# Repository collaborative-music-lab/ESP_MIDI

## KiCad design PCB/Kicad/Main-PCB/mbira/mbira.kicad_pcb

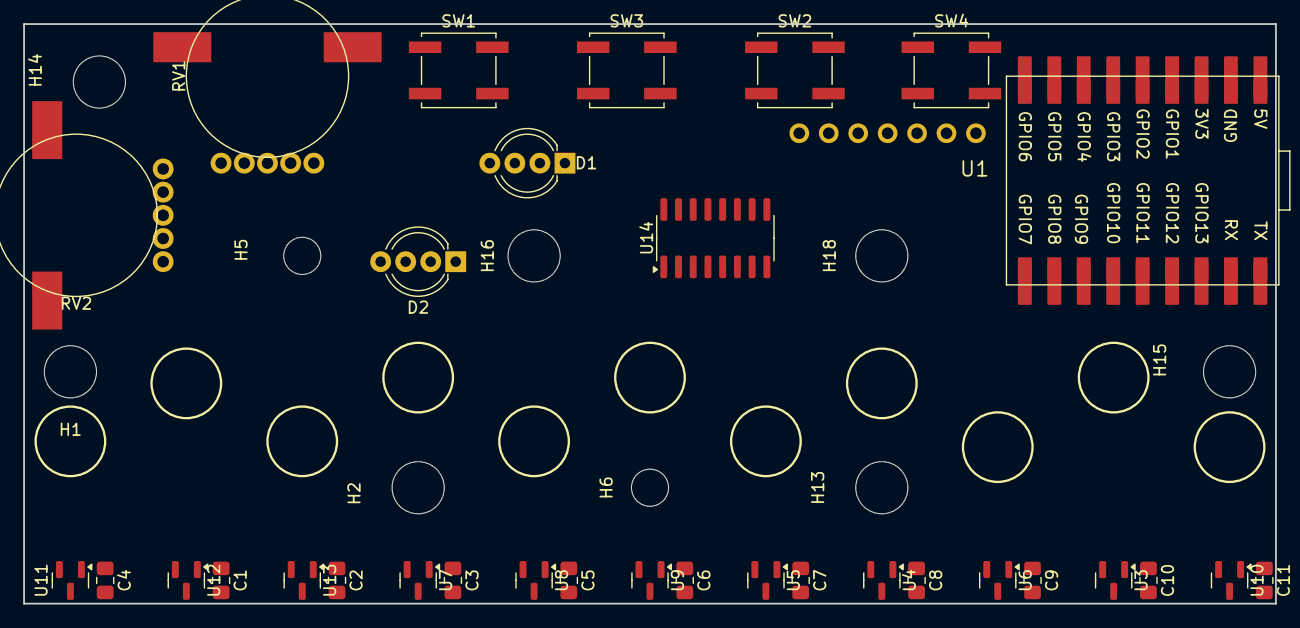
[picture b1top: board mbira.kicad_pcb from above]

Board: 2 copper layers, 108.0 x 50.0 mm, 42 parts (0 on the bottom side), 18 nets, no tracks yet.

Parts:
C1, C2, C3, C4, C5, C6, C7, C8, C9, C10, C11: 0.1uF; C_0805_2012Metric_Pad1.18x1.45mm_HandSolder
D1, D2: WS2812B; LED_D5.0mm-4_RGB_Wide_Pins
H1, H2, H13, H14, H15, H16, H18: MountingHole; MountingHole_4.5mm
H5, H6: MountingHole; MountingHole_3.2mm_M3_ISO14580
RV1, RV2: R_Potentiometer_Dual; potentiometer_wheel_10mm_SMD-shield
SW1, SW2, SW3, SW4: SW_DPST; SW_Push_1P1T_NO_CK_KSC6xxJ
U1: LSM6DS3_Breakout; LSM6DS3_Breakout_oneSide
U2: Wifiduino-ESP32S3-SMD
U3, U4, U5, U6, U7, U8, U9, U10, U11, U12, U13: SM351LT; SOT-23
U14: MCP3208; SOIC-16_3.9x9.9mm_P1.27mm

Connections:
+3.3V: C1.1, C2.1, C3.1, C4.1, C5.1, C6.1, C7.1, C8.1, C9.1, C10.1, C11.1, D1.3 (VDD), D2.3 (VDD), RV1.1 (1A), RV2.1 (1A), U1.1 (VIN), U2.3 (3V3), U3.1 (VCC), U4.1 (VCC), U5.1 (VCC), U6.1 (VCC), U7.1 (VCC), U8.1 (VCC), U9.1 (VCC), U10.1 (VCC), U11.1 (VCC), U12.1 (VCC), U13.1 (VCC)
/A0: U2.4 (GPIO1/ADC1_CH0), U3.2 (OUTPUT)
/A1: U2.5 (GPIO2/ADC1_CH1), U4.2 (OUTPUT)
/A2: U2.6 (GPIO3/ADC1_CH2), U5.2 (OUTPUT)
/A3: U2.7 (GPIO4/ADC1_CH3), U6.2 (OUTPUT)
/A4: U2.8 (GPIO5/ADC1_CH4), U7.2 (OUTPUT)
/A5: U2.9 (GPIO6/ADC1_CH5), U8.2 (OUTPUT)
/A6: U2.10 (GPIO7/ADC1_CH6), U9.2 (OUTPUT)
/A7: U2.11 (GPIO8/ADC1_CH7), U10.2 (OUTPUT)
/A8: U2.12 (GPIO9/ADC1_CH8), U11.2 (OUTPUT)
/A9: U2.13 (GPIO10/ADC1_CH9), U12.2 (OUTPUT)
/A10: U2.16 (GPIO13/ADC2_CH2), U13.2 (OUTPUT)
/A11: RV1.6 (Shield), RV2.6 (Shield), U2.15 (GPIO12/ADC2_CH1)
/D0: D1.4 (DIN), U2.14 (GPIO11/ADC2_CH0)
/SCL: U1.4 (SCL), U2.18 (GPIO43/U0TXD)
/SDA: U1.5 (SDA), U2.17 (GPIO44/U0RXD)
GND: C1.2, C2.2, C3.2, C4.2, C5.2, C6.2, C7.2, C8.2, C9.2, C10.2, C11.2, D1.2 (VSS), D2.2 (VSS), RV1.5 (Common), RV2.5 (Common), U1.3 (GND), U2.2 (GND), U3.3 (GND), U4.3 (GND), U5.3 (GND), U6.3 (GND), U7.3 (GND), U8.3 (GND), U9.3 (GND), U10.3 (GND), U11.3 (GND), U12.3 (GND), U13.3 (GND)
unnamed: D1.1 (DOUT), D2.4 (DIN)

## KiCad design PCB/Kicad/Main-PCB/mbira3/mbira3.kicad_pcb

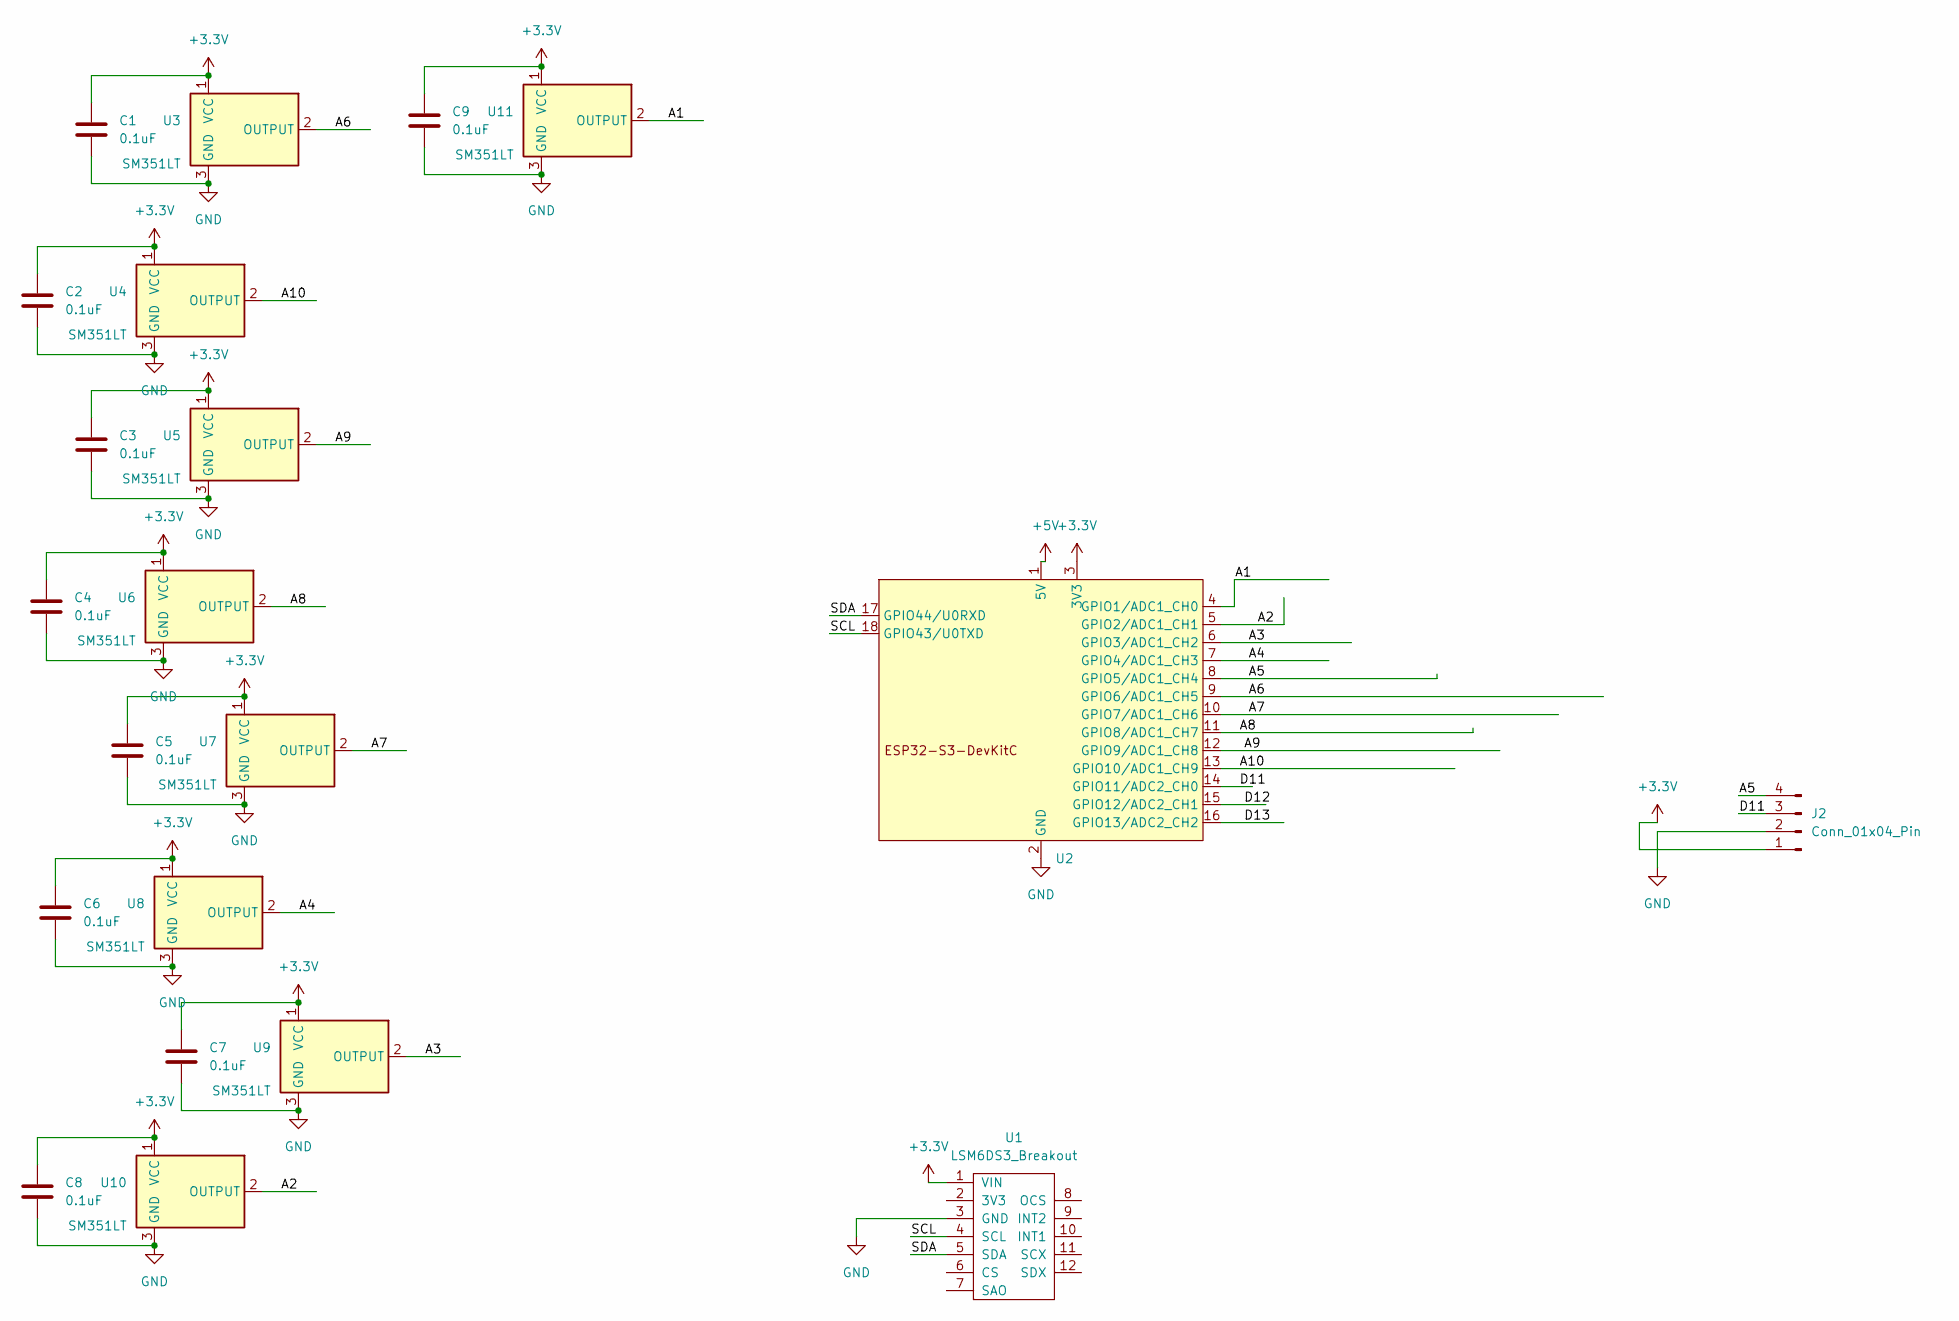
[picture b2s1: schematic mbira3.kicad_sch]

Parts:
C1, C2, C3, C4, C5, C6, C7, C8, C9: 0.1uF; C_0805_2012Metric_Pad1.18x1.45mm_HandSolder
J2: Conn_01x04_Pin; PinHeader_1x04_P1.27mm_Vertical
U1: LSM6DS3_Breakout; LSM6DS3_Breakout_oneSide
U2: Wifiduino-ESP32S3-SMD
U3, U4, U5, U6, U7, U8, U9, U10, U11: SM351LT; SOT-23

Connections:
+3.3V: C1.1, C2.1, C3.1, C4.1, C5.1, C6.1, C7.1, C8.1, C9.1, J2.1, U1.1 (VIN), U2.3 (3V3), U3.1 (VCC), U4.1 (VCC), U5.1 (VCC), U6.1 (VCC), U7.1 (VCC), U8.1 (VCC), U9.1 (VCC), U10.1 (VCC), U11.1 (VCC)
+5V: U2.1 (5V)
/A1: U2.4 (GPIO1/ADC1_CH0), U11.2 (OUTPUT)
/A2: U2.5 (GPIO2/ADC1_CH1), U10.2 (OUTPUT)
/A3: U2.6 (GPIO3/ADC1_CH2), U9.2 (OUTPUT)
/A4: U2.7 (GPIO4/ADC1_CH3), U8.2 (OUTPUT)
/A5: J2.4, U2.8 (GPIO5/ADC1_CH4)
/A6: U2.9 (GPIO6/ADC1_CH5), U3.2 (OUTPUT)
/A7: U2.10 (GPIO7/ADC1_CH6), U7.2 (OUTPUT)
/A8: U2.11 (GPIO8/ADC1_CH7), U6.2 (OUTPUT)
/A9: U2.12 (GPIO9/ADC1_CH8), U5.2 (OUTPUT)
/A10: U2.13 (GPIO10/ADC1_CH9), U4.2 (OUTPUT)
/D11: J2.3, U2.14 (GPIO11/ADC2_CH0)
/D12: U2.15 (GPIO12/ADC2_CH1)
/D13: U2.16 (GPIO13/ADC2_CH2)
/SCL: U1.4 (SCL), U2.18 (GPIO43/U0TXD)
/SDA: U1.5 (SDA), U2.17 (GPIO44/U0RXD)
GND: C1.2, C2.2, C3.2, C4.2, C5.2, C6.2, C7.2, C8.2, C9.2, J2.2, U1.3 (GND), U2.2 (GND), U3.3 (GND), U4.3 (GND), U5.3 (GND), U6.3 (GND), U7.3 (GND), U8.3 (GND), U9.3 (GND), U10.3 (GND), U11.3 (GND)

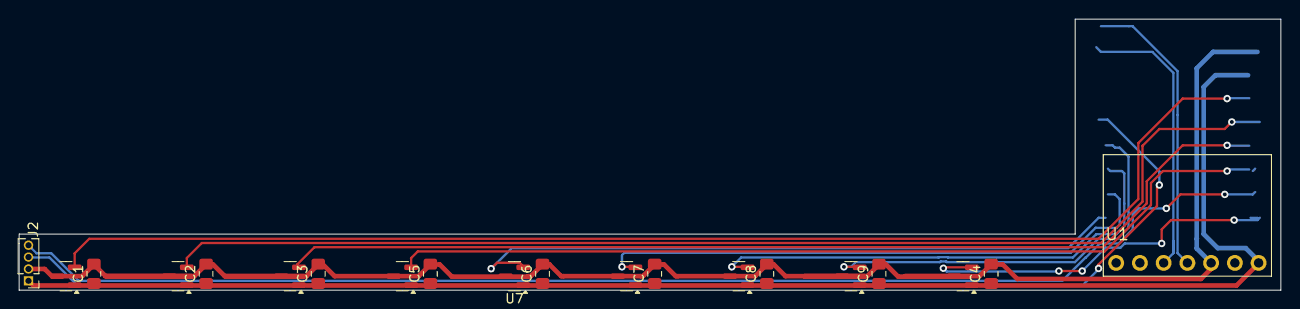
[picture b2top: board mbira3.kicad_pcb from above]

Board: 2 copper layers, 135.0 x 29.0 mm, 21 parts (1 on the bottom side), 15 nets.

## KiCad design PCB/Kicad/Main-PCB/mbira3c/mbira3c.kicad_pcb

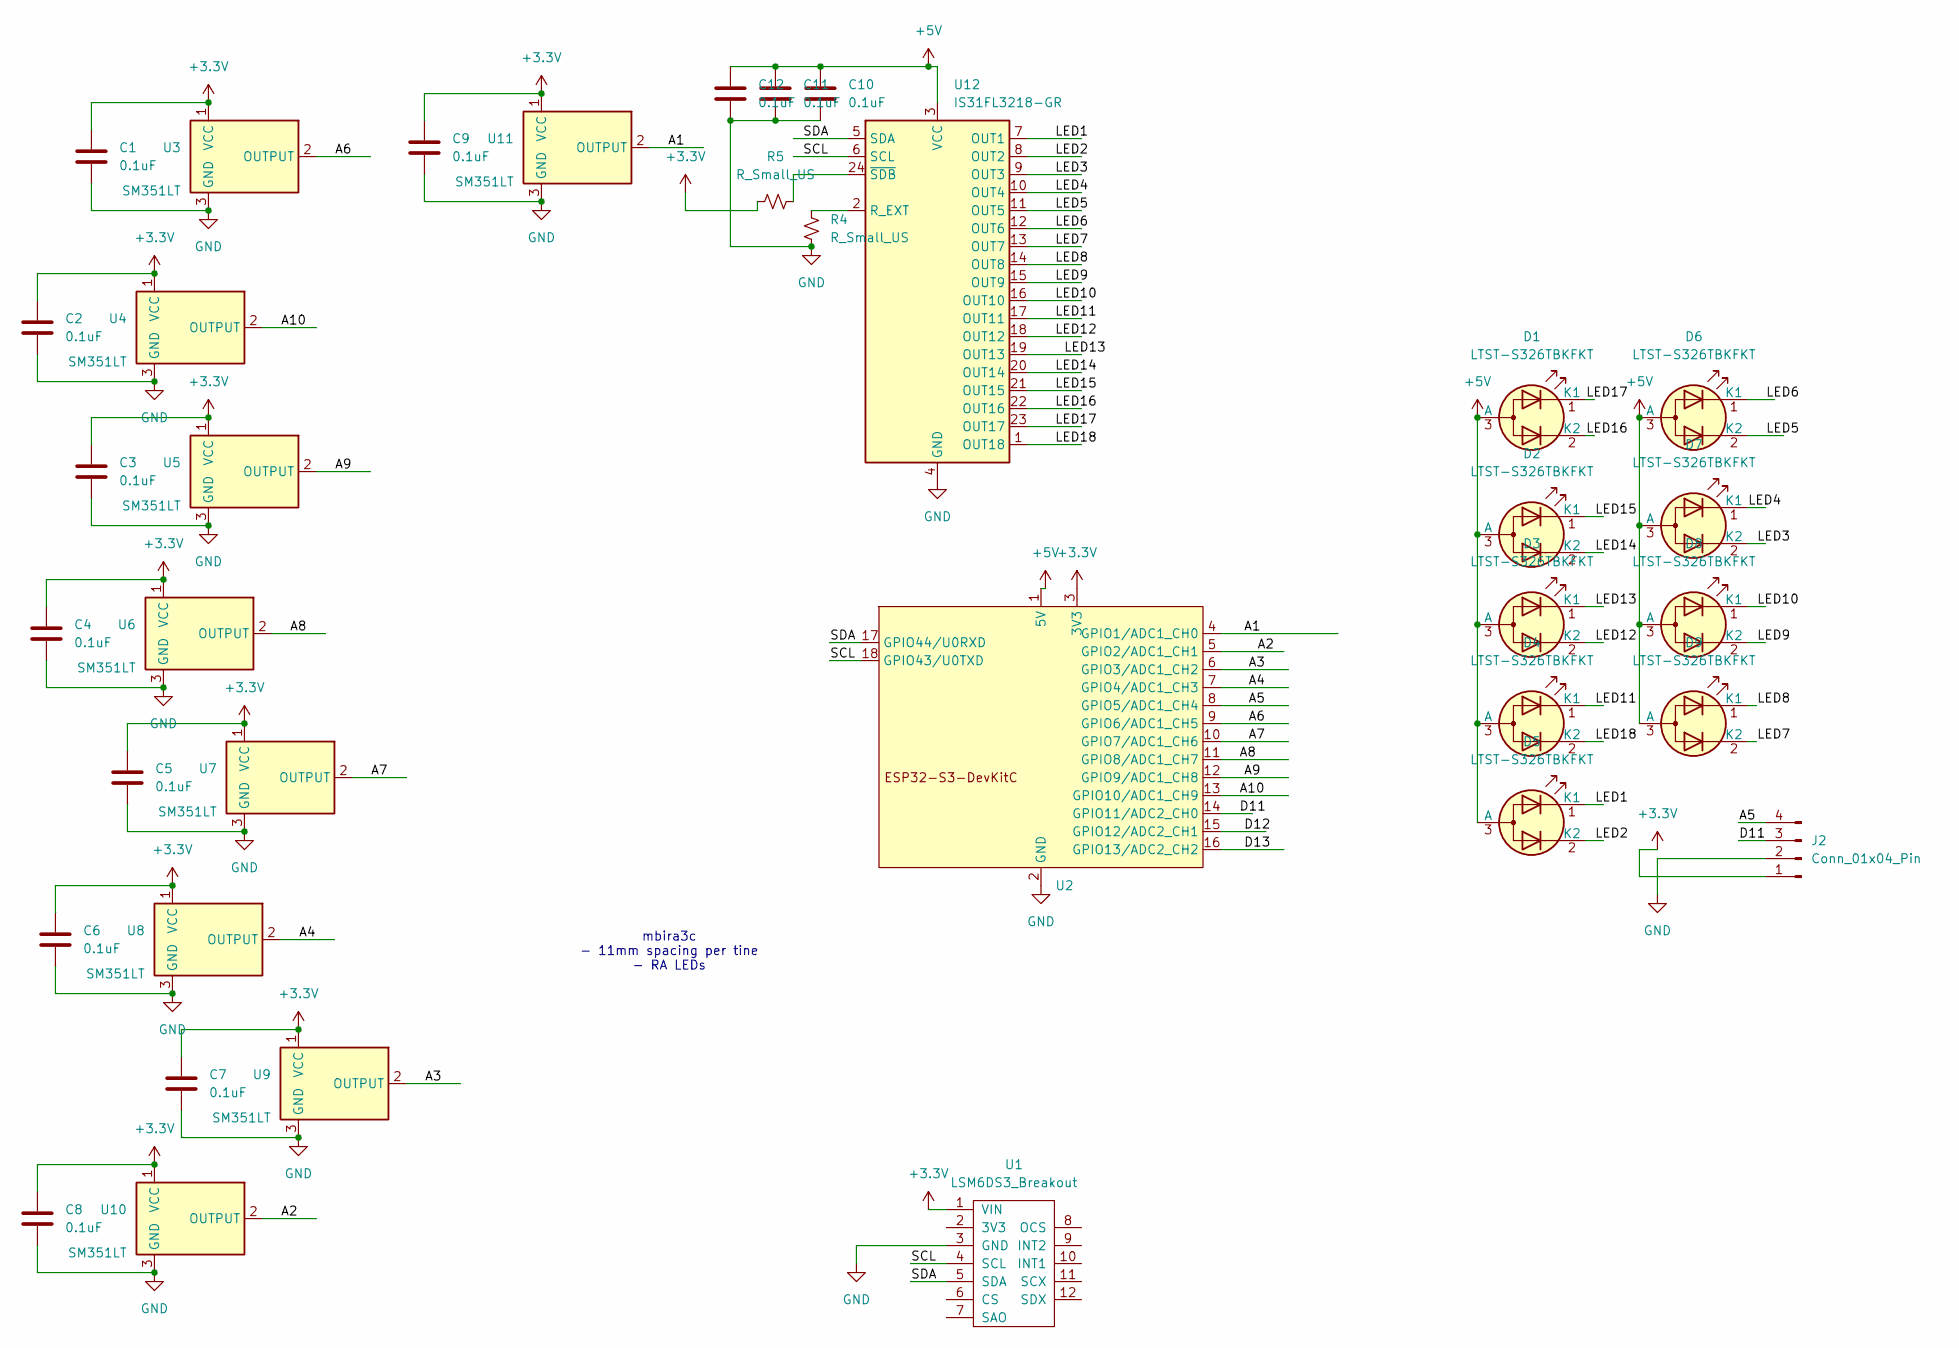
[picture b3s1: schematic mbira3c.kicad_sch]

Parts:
C1, C2, C3, C4, C5, C6, C7, C8, C9, C10, C11, C12: 0.1uF; C_0805_2012Metric_Pad1.18x1.45mm_HandSolder
D1, D2, D3, D4, D5, D6, D7, D8, D9: LTST-S326TBKFKT; LED_LiteOn_LTST-S326
J2: Conn_01x04_Pin; PinHeader_1x04_P1.27mm_Vertical
R4, R5: R_Small_US; R_0805_2012Metric
U1: LSM6DS3_Breakout; LSM6DS3_Breakout_oneSide
U2: Wifiduino-ESP32S3-SMD
U3, U4, U5, U6, U7, U8, U9, U10, U11: SM351LT; SOT-23
U12: IS31FL3218-GR; SOP-24_7.5x15.4mm_P1.27mm

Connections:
+3.3V: C1.1, C2.1, C3.1, C4.1, C5.1, C6.1, C7.1, C8.1, C9.1, J2.1, R5.1, U1.1 (VIN), U2.3 (3V3), U3.1 (VCC), U4.1 (VCC), U5.1 (VCC), U6.1 (VCC), U7.1 (VCC), U8.1 (VCC), U9.1 (VCC), U10.1 (VCC), U11.1 (VCC)
+5V: C10.1, C11.1, C12.1, D1.3 (A), D2.3 (A), D3.3 (A), D4.3 (A), D5.3 (A), D6.3 (A), D7.3 (A), D8.3 (A), D9.3 (A), U2.1 (5V), U12.3 (VCC)
/A1: U2.4 (GPIO1/ADC1_CH0), U11.2 (OUTPUT)
/A2: U2.5 (GPIO2/ADC1_CH1), U10.2 (OUTPUT)
/A3: U2.6 (GPIO3/ADC1_CH2), U9.2 (OUTPUT)
/A4: U2.7 (GPIO4/ADC1_CH3), U8.2 (OUTPUT)
/A5: J2.4, U2.8 (GPIO5/ADC1_CH4)
/A6: U2.9 (GPIO6/ADC1_CH5), U3.2 (OUTPUT)
/A7: U2.10 (GPIO7/ADC1_CH6), U7.2 (OUTPUT)
/A8: U2.11 (GPIO8/ADC1_CH7), U6.2 (OUTPUT)
/A9: U2.12 (GPIO9/ADC1_CH8), U5.2 (OUTPUT)
/A10: U2.13 (GPIO10/ADC1_CH9), U4.2 (OUTPUT)
/D11: J2.3, U2.14 (GPIO11/ADC2_CH0)
/D12: U2.15 (GPIO12/ADC2_CH1)
/D13: U2.16 (GPIO13/ADC2_CH2)
/LED1: D5.1 (K1), U12.7 (OUT1)
/LED2: D5.2 (K2), U12.8 (OUT2)
/LED3: D7.2 (K2), U12.9 (OUT3)
/LED4: D7.1 (K1), U12.10 (OUT4)
/LED5: D6.2 (K2), U12.11 (OUT5)
/LED6: D6.1 (K1), U12.12 (OUT6)
/LED7: D9.2 (K2), U12.13 (OUT7)
/LED8: D9.1 (K1), U12.14 (OUT8)
/LED9: D8.2 (K2), U12.15 (OUT9)
/LED10: D8.1 (K1), U12.16 (OUT10)
/LED11: D4.1 (K1), U12.17 (OUT11)
/LED12: D3.2 (K2), U12.18 (OUT12)
/LED13: D3.1 (K1), U12.19 (OUT13)
/LED14: D2.2 (K2), U12.20 (OUT14)
/LED15: D2.1 (K1), U12.21 (OUT15)
/LED16: D1.2 (K2), U12.22 (OUT16)
/LED17: D1.1 (K1), U12.23 (OUT17)
/LED18: D4.2 (K2), U12.1 (OUT18)
/SCL: U1.4 (SCL), U2.18 (GPIO43/U0TXD), U12.6 (SCL)
/SDA: U1.5 (SDA), U2.17 (GPIO44/U0RXD), U12.5 (SDA)
GND: C1.2, C2.2, C3.2, C4.2, C5.2, C6.2, C7.2, C8.2, C9.2, C10.2, C11.2, C12.2, J2.2, R4.2, U1.3 (GND), U2.2 (GND), U3.3 (GND), U4.3 (GND), U5.3 (GND), U6.3 (GND), U7.3 (GND), U8.3 (GND), U9.3 (GND), U10.3 (GND), U11.3 (GND), U12.4 (GND)
unnamed: R4.1, U12.2 (R_EXT)
unnamed: R5.2, U12.24 (~SDB)

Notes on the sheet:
mbira3c - 11mm spacing per tine - RA LEDs

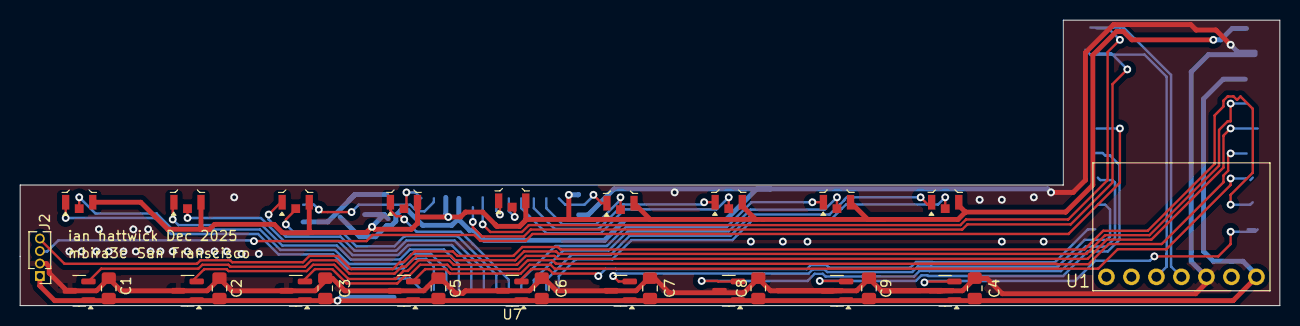
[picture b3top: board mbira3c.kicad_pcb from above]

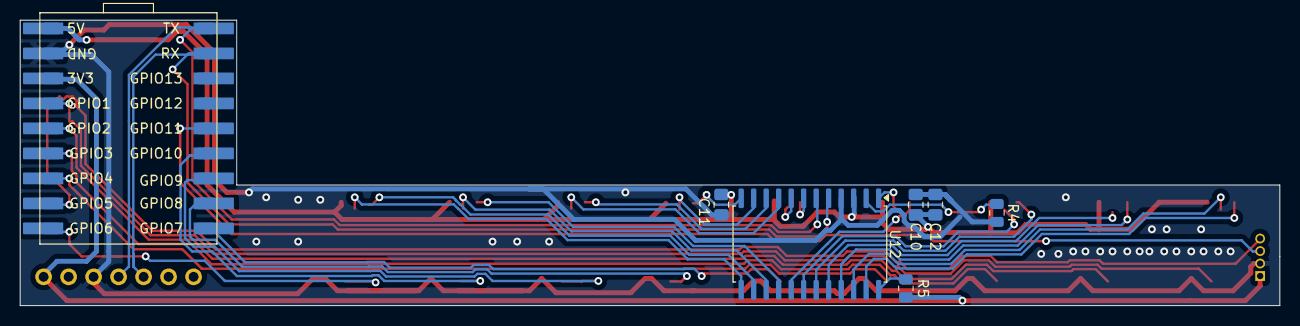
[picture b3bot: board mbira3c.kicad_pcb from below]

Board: 2 copper layers, 128.0 x 29.0 mm, 36 parts (7 on the bottom side), 36 nets.

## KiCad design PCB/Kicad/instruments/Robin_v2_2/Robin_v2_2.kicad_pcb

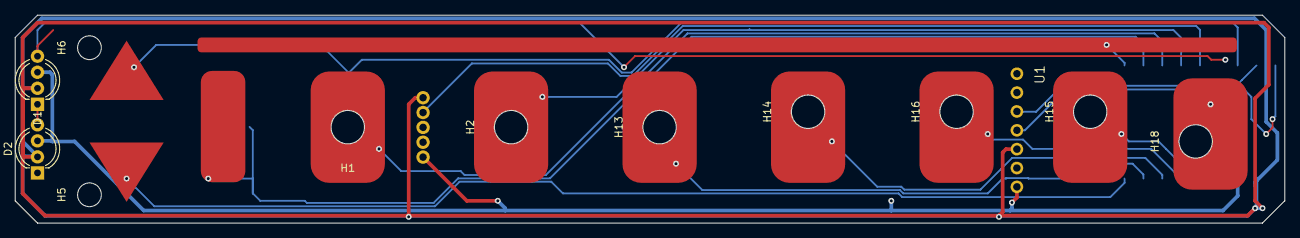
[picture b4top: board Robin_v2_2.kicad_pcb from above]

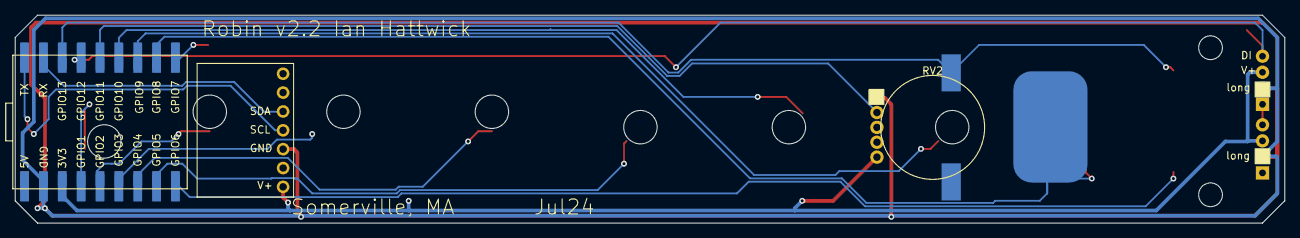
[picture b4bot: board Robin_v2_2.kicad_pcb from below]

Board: 2 copper layers, 171.0 x 28.0 mm, 26 parts (3 on the bottom side), 18 nets.

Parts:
D1, D2: WS2812B; LED_D5.0mm-4_RGB_Wide_Pins
H1, H2, H13, H14, H15, H16, H18: MountingHole; MountingHole_4.5mm
H5, H6: MountingHole; MountingHole_3.2mm_M3_ISO14580
RV2: R_Potentiometer_Dual; potentiometer_wheel_10mm_SMD-shield
TP1, TP2, TP3, TP4, TP5, TP6, TP7, TP10: TestPoint; recorder-touchpad
TP8, TP12: TestPoint; recorder-touchpad-alt-up
TP9: TestPoint; recorder-touchtrack_120mm
TP11: TestPoint; recorder-touchpad-narrow
U1: LSM6DS3_Breakout; LSM6DS3_Breakout_oneSide
U2: Wifiduino-ESP32S3-SMD

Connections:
+3.3V: D1.3 (VDD), D2.3 (VDD), RV2.1 (1A), U1.1 (VIN), U2.3 (3V3)
/A0: TP10.1, U2.4 (GPIO1/ADC1_CH0)
/A1: TP7.1, U2.5 (GPIO2/ADC1_CH1)
/A2: TP6.1, U2.6 (GPIO3/ADC1_CH2)
/A3: TP5.1, U2.7 (GPIO4/ADC1_CH3)
/A4: TP4.1, U2.8 (GPIO5/ADC1_CH4)
/A5: TP8.1, U2.9 (GPIO6/ADC1_CH5)
/A6: TP9.1, U2.10 (GPIO7/ADC1_CH6)
/A7: TP1.1, TP11.1, U2.11 (GPIO8/ADC1_CH7)
/A8: TP2.1, U2.12 (GPIO9/ADC1_CH8)
/A9: TP3.1, U2.13 (GPIO10/ADC1_CH9)
/A10: RV2.6 (Shield), TP12.1, U2.16 (GPIO13/ADC2_CH2)
/D0: RV2.4 (1-Wiper), U2.14 (GPIO11/ADC2_CH0)
/D1: D1.4 (DIN), U2.15 (GPIO12/ADC2_CH1)
/SCL: U1.4 (SCL), U2.18 (GPIO43/U0TXD)
/SDA: U1.5 (SDA), U2.17 (GPIO44/U0RXD)
GND: D1.2 (VSS), D2.2 (VSS), RV2.5 (Common), U1.3 (GND), U2.2 (GND)
unnamed: D1.1 (DOUT), D2.4 (DIN)

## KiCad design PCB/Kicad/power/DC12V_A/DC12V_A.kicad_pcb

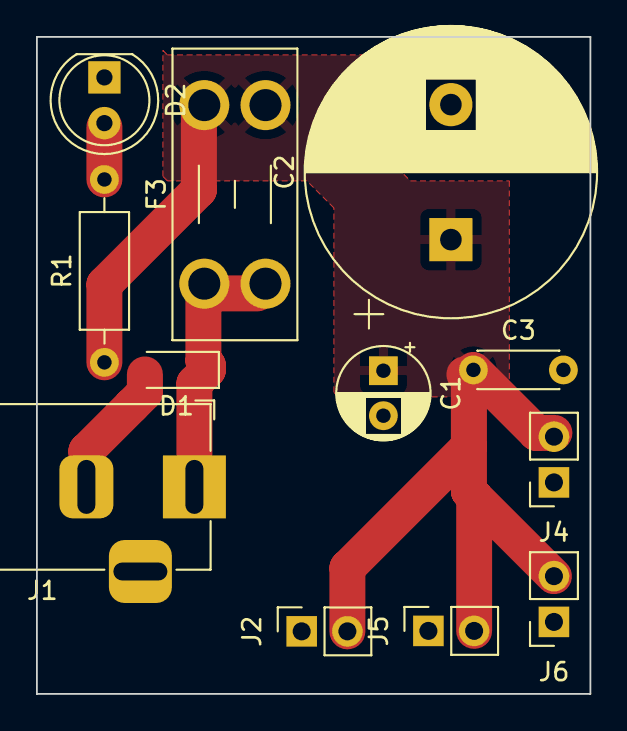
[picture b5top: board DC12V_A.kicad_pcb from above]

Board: 2 copper layers, 30.8 x 36.5 mm, 12 parts (0 on the bottom side), 4 nets.

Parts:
C1: 1uF; CP_Radial_D5.0mm_P2.50mm
C2: 3300uF; CP_Radial_D16.0mm_P7.50mm
C3: 0.1uF; C_Disc_D4.3mm_W1.9mm_P5.00mm
D1: TPSMF4L15A; D_SOD-123
D2: LED; LED_D5.0mm
F3: Fuse; Fuseholder_Blade_Mini_Keystone_3568
J1: Barrel_Jack_Switch; BarrelJack_Horizontal
J2, J4, J5, J6: Conn_01x02_Pin; PinSocket_1x02_P2.54mm_Vertical
R1: R_Small_US; R_Axial_DIN0207_L6.3mm_D2.5mm_P10.16mm_Horizontal

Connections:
+12V: C1.1, C2.1, C3.1, F3.2, J2.2, J4.2, J5.2, J6.2, R1.1
GND: C1.2, C2.2, C3.2, D1.2 (A), D2.1 (K), J1.2, J2.1, J4.1, J5.1, J6.1
unnamed: D1.1 (K), F3.1, J1.1
unnamed: D2.2 (A), R1.2
